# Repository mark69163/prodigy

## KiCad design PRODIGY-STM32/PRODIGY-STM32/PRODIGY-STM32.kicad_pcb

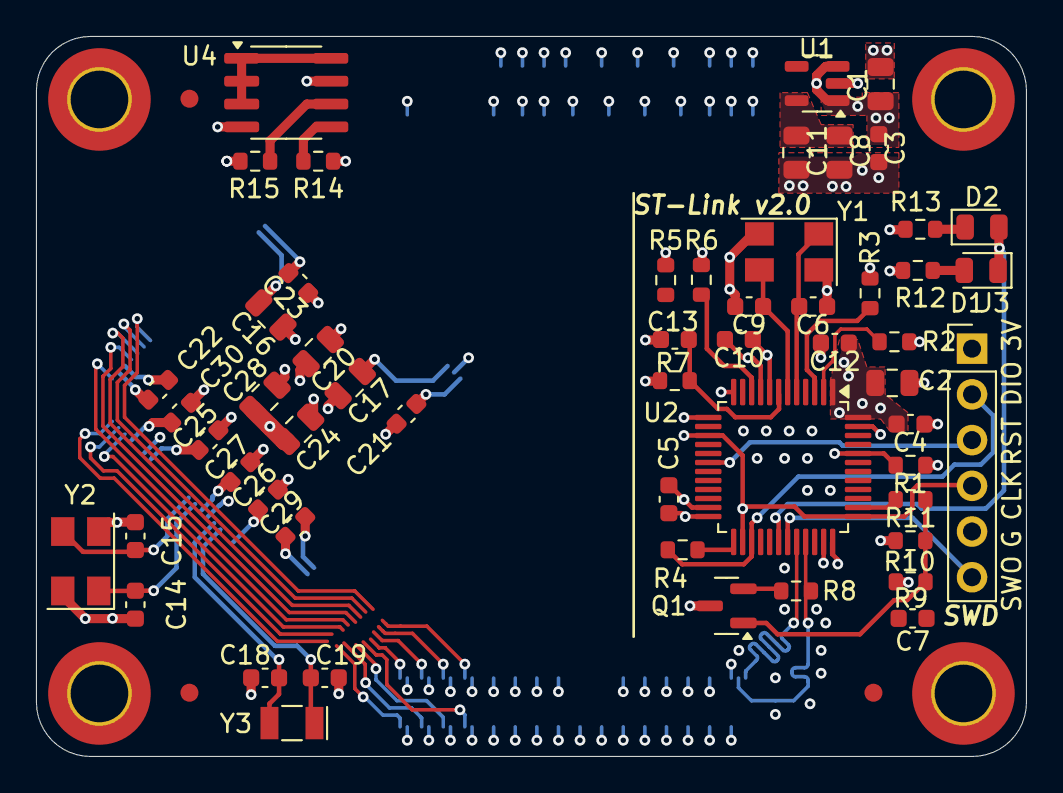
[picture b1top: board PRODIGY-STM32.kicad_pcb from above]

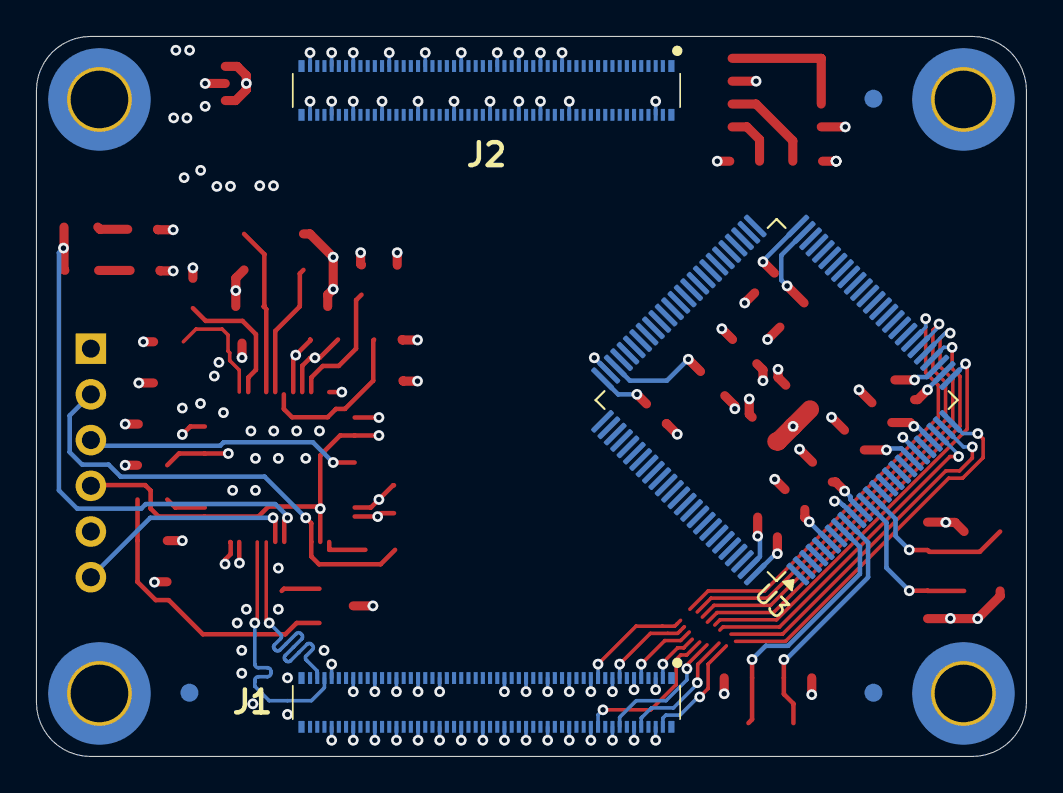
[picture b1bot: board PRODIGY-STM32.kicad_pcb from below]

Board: 4 copper layers, 55.0 x 40.0 mm, 68 parts (6 on the bottom side), 106 nets.

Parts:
C1, C2, C8, C11, C20, C24, C28: 10uF; C_0805_2012Metric
C3, C4, C5, C7, C10, C12, C13, C21, C22, C23, C25, C26, C27, C29, C30: 100nF; C_0603_1608Metric
C6, C9: 10pF; C_0603_1608Metric
C14, C15: 4.7pF; C_0603_1608Metric
C16, C17: 2.2uF; C_0805_2012Metric
C18, C19: 2.7pF; C_0603_1608Metric
D1, D2: LED; LED_0805_2012Metric
FID1, FID2, FID3, FID4, FID5, FID6: Fiducial; Fiducial_1mm_Mask3mm
H1, H2, H3, H4: MountingHole; MountingHole_3.2mm_M3_ISO7380_Pad_TopBottom
J1, J2: DF40C-100DP-04V-51; DF40C100DP04V51
J3: Conn_ARM_SWD_TagConnect_TC2030; PinHeader_1x06_P2.54mm_Vertical
Q1: BC850; SOT-23
R1, R7: 100k; R_0603_1608Metric
R2, R9, R10: 10k; R_0603_1608Metric
R3, R14, R15: DNP; R_0603_1608Metric
R4, R11: 100; R_0603_1608Metric
R5, R6: 4k7; R_0603_1608Metric
R8: 1k5; R_0603_1608Metric
R12, R13: 1k; R_0603_1608Metric
U1: AP2112K-3.3; SOT-23-5
U2: STM32F103C8Tx; LQFP-48_7x7mm_P0.5mm
U3: STM32F407VGTx; LQFP-100_14x14mm_P0.5mm
U4: M24C32-WMN6TP; SOIC-8_3.9x4.9mm_P1.27mm
Y1, Y2: 8MHz; Crystal_SMD_5032-4Pin_5.0x3.2mm
Y3: 32.768kHz; Crystal_SMD_MicroCrystal_CC7V-T1A-2Pin_3.2x1.5mm

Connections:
+3V3: C20.1, C21.1, C22.1, C23.1, C24.1, C25.1, C26.1, C27.1, C28.1, C29.1, C30.1, J2.12, J2.14, J2.16, J2.18, R14.1, R15.1, U3.6 (VBAT), U3.11 (VDD), U3.19 (VDD), U3.22 (VDDA), U3.28 (VDD), U3.50 (VDD), U3.75 (VDD), U3.100 (VDD), U4.1 (E0), U4.2 (E1), U4.3 (E2), U4.8 (VCC)
+5V: C1.1, C3.1, J2.13, J2.15, J2.17, J2.19, J2.21, J2.23, U1.1 (VIN), U1.3 (EN)
/Connector-1/ANALOG_BREAKOUT_PIEZO: J1.2, U3.31 (PA6)
/Connector-1/ANALOG_BREAKOUT_PT100: J1.8, U3.32 (PA7)
/Connector-1/ANALOG_HEATER_TEMPERATURE: J1.14, U3.30 (PA5)
/Connector-1/ANALOG_JOYSTICK_X: J1.13, U3.25 (PA2)
/Connector-1/ANALOG_JOYSTICK_Y: J1.7, U3.26 (PA3)
/Connector-1/ANALOG_MICROPHONE: J1.1, U3.29 (PA4)
/Connector-1/ANALOG_PHOTOTRANSISTOR: J1.19, U3.24 (PA1)
/Connector-1/ANALOG_POTENTIOMETER: J1.20, U3.23 (PA0)
/Connector-1/CAN_EN: J1.86, U3.84 (PD3)
/Connector-1/CAN_OUT_RX1: J1.83, U3.81 (PD0)
/Connector-1/CAN_OUT_TX1: J1.85, U3.82 (PD1)
/Connector-1/CAN_SILENT: J1.84, U3.85 (PD4)
/Connector-1/DIGITAL_BUTTON_IN_0: J1.53, U3.57 (PD10)
/Connector-1/DIGITAL_BUTTON_IN_1: J1.51, U3.58 (PD11)
/Connector-1/DIGITAL_BUTTON_IN_2: J1.49, U3.59 (PD12)
/Connector-1/DIGITAL_BUTTON_IN_3: J1.47, U3.60 (PD13)
/Connector-1/DIGITAL_BUZZER_OUT: J1.42, U3.36 (PB1)
/Connector-1/DIGITAL_HEATER_OUT: J1.48, U3.37 (PB2)
/Connector-1/DIGITAL_IR_EMITTER: J1.67, U3.33 (PC4)
/Connector-1/DIGITAL_IR_RECEIVER: J1.65, U3.34 (PC5)
/Connector-1/DIGITAL_LED_OUT_0: J1.43, U3.88 (PD7)
/Connector-1/DIGITAL_LED_OUT_1: J1.41, U3.61 (PD14)
/Connector-1/DIGITAL_LED_OUT_2: J1.44, U3.62 (PD15)
/Connector-1/DIGITAL_NEOPIXEL_OUT: J1.61, U3.35 (PB0)
/Connector-1/DIGITAL_RGB_B: J1.55, U3.4 (PE5)
/Connector-1/DIGITAL_RGB_G: J1.57, U3.3 (PE4)
/Connector-1/DIGITAL_RGB_R: J1.59, U3.5 (PE6)
/Connector-1/I2C_INTERRUPT_ACCEL: J1.73, U3.91 (PB5)
/Connector-1/I2C_INTERRUPT_KEYPAD: J1.71, U3.95 (PB8)
/Connector-1/MOTOR_CC_IN_1: J1.35, U3.97 (PE0)
/Connector-1/MOTOR_CC_IN_2: J1.36, U3.98 (PE1)
/Connector-1/MOTOR_PWM_OUT_1: J1.37, U3.1 (PE2)
/Connector-1/MOTOR_PWM_OUT_2: J1.38, U3.2 (PE3)
/Connector-1/SERIAL_OUT_RX1: J1.91, U3.68 (PA9)
/Connector-1/SERIAL_OUT_RX2: J1.90, U3.87 (PD6)
/Connector-1/SERIAL_OUT_TX1: J1.89, U3.69 (PA10)
/Connector-1/SERIAL_OUT_TX2: J1.92, U3.86 (PD5)
/Connector-1/SPI_CS_BREAKOUT: J1.72, U3.96 (PB9)
/Connector-1/SPI_CS_NFC: J1.56, U3.54 (PB15)
/Connector-1/SPI_CS_SEVENSEG: J1.68, U3.48 (PB11)
/Connector-1/SPI_CS_TFT: J1.66, U3.51 (PB12)
/Connector-1/SPI_IRQ_NFC: J1.54, U3.15 (PC0)
/Connector-1/SPI_MISO: J1.78, U3.17 (PC2)
/Connector-1/SPI_MOSI: J1.80, U3.18 (PC3)
/Connector-1/SPI_RST_NFC: J1.50, U3.16 (PC1)
/Connector-1/SPI_SCK: J1.74, U3.47 (PB10)
/Connector-1/SPI_TFT_DC: J1.62, U3.52 (PB13)
/Connector-1/SPI_TFT_RESET: J1.60, U3.53 (PB14)
/Connector-1/USB_DP-: J1.97, U2.32 (PA11)
/Connector-1/USB_HOST_ENABLE: J1.100, U3.77 (PA15)
/Connector-1/USB_HOST_FAULT: J1.99, U3.67 (PA8)
/Connector-1/USB_HOST_OUT_P+: J1.96, U3.71 (PA12)
/Connector-1/USB_HOST_OUT_P-: J1.98, U3.70 (PA11)
/Connector-2/MCU_GPIO_6: J2.72, U3.7 (PC13)
/Connector-2/MCU_GPIO_7: J2.63, U3.38 (PE7)
/Connector-2/MCU_GPIO_8: J2.61, U3.39 (PE8)
/Connector-2/MCU_GPIO_9: J2.62, U3.40 (PE9)
/Connector-2/MCU_GPIO_10: J2.58, U3.41 (PE10)
/Connector-2/MCU_GPIO_11: J2.64, U3.42 (PE11)
/Connector-2/MCU_GPIO_12: J2.69, U3.43 (PE12)
/Connector-2/MCU_GPIO_13: J2.74, U3.44 (PE13)
/Connector-2/MCU_GPIO_14: J2.45, U3.45 (PE14)
/Connector-2/MCU_GPIO_15: J2.49, U3.46 (PE15)
/Connector-2/MCU_RESET: J2.2, U3.14 (NRST)
/Connector-2/MCU_VREF: J2.24, U3.21 (VREF+)
/Connector-2/SD_CLK: J2.43, U3.80 (PC12)
/Connector-2/SD_CMD: J2.40, U3.83 (PD2)
/Connector-2/SD_DAT0: J2.37, U3.65 (PC8)
/Connector-2/SD_DAT1: J2.33, U3.66 (PC9)
/Connector-2/SD_DAT2: J2.31, U3.78 (PC10)
/Connector-2/SD_DAT3: J2.39, U3.79 (PC11)
/Connector-2/SD_DET: J2.26, U3.63 (PC6)
/Connector-2/SD_Enable: J2.25, U3.64 (PC7)
/mcu/BOOT: R1.1, U2.44 (BOOT0), U3.94 (BOOT0)
/mcu/SCL: J1.77, R15.2, U3.92 (PB6), U4.6 (SCL)
/mcu/SDA: J1.79, R14.2, U3.93 (PB7), U4.5 (SDA)
/mcu/T_RX: U2.13 (PA3), U3.56 (PD9)
/mcu/T_TX: U2.12 (PA2), U3.55 (PD8)
/st-link-v2/+3V3_STLINK: C2.1, C4.1, C5.1, C7.1, C8.1, C10.1, C11.1, C12.1, J3.1 (VCC), Q1.3 (C), R5.1, R7.1, R9.1, R12.1, U1.5 (VOUT), U2.1 (VBAT), U2.9 (VDDA), U2.24 (VDD), U2.36 (VDD), U2.48 (VDD)
/st-link-v2/CLK: J3.4 (SWCLK), U2.15 (PA5), U2.26 (PB13), U2.37 (PA14), U3.76 (PA14)
/st-link-v2/LED: D1.1 (K), D2.2 (A), U2.30 (PA9)
/st-link-v2/RENUM: R11.2, U2.38 (PA15)
/st-link-v2/RESET: C13.1, R7.2, U2.7 (NRST)
/st-link-v2/T_DIO: J3.2 (SWDIO), R4.1, U2.27 (PB14), U3.72 (PA13)
/st-link-v2/T_RST: J3.3 (~RESET), U2.18 (PB0), U3.90 (PB4)
/st-link-v2/T_SWO: J3.6 (SWO), U2.31 (PA10), U3.89 (PB3)
/st-link-v2/USB_D+: J1.95, R8.2, U2.33 (PA12)
GND: C1.2, C2.2, C3.2, C4.2, C5.2, C6.2, C7.2, C8.2, C9.2, C10.2, C11.2, C12.2, C13.2, C14.2, C15.2, C16.2, C17.2, C18.2, C19.2, C20.2, C21.2, C22.2, C23.2, C24.2, C25.2, C26.2, C27.2, C28.2, C29.2, C30.2, J1.3, J1.4, J1.9, J1.10, J1.15, J1.16, J1.21, J1.22, J1.27, J1.28, J1.33, J1.34, J1.39, J1.40, J1.45, J1.46, J1.52, J1.58, J1.63, J1.64, J1.69, J1.70, J1.75, J1.76, J1.81, J1.82, J1.87, J1.88, J1.93, J1.94, J2.4, J2.28, J2.29, J2.35, J2.36, J2.41, J2.42, J2.47, J2.50, J2.57, J2.60, J2.67, J2.70, J2.77, J2.80, J2.87, J2.88, J2.93, J2.94, J2.99, J2.100, J3.5 (GND), R1.2, R2.2, R3.2, R6.2, R10.2, R13.2, U1.2 (GND), U2.8 (VSSA), U2.23 (VSS), U2.35 (VSS), U2.47 (VSS), U3.10 (VSS), U3.20 (VSSA), U3.27 (VSS), U3.74 (VSS), U3.99 (VSS), U4.4 (VSS), U4.7 (~WC), Y1.2, Y1.4, Y2.2, Y2.4
unnamed: D1.2 (A), R12.2
unnamed: D2.1 (K), R13.1
unnamed: Q1.1 (B), R9.2, R10.1, R11.1
unnamed: Q1.2 (E), R8.1
unnamed: R5.2, R6.1, U2.10 (PA0)
unnamed: R4.2, U2.25 (PB12)
unnamed: R2.1, U2.2 (PC13)
unnamed: R3.1, U2.3 (PC14)
unnamed: C6.1, U2.5 (PD0), Y1.1
unnamed: C9.1, U2.6 (PD1), Y1.3
unnamed: C19.1, U3.8 (PC14), Y3.1
unnamed: C18.1, U3.9 (PC15), Y3.2
unnamed: C14.1, U3.12 (PH0), Y2.1
unnamed: C15.1, U3.13 (PH1), Y2.3
unnamed: C16.1, U3.49 (VCAP_1)
unnamed: C17.1, U3.73 (VCAP_2)

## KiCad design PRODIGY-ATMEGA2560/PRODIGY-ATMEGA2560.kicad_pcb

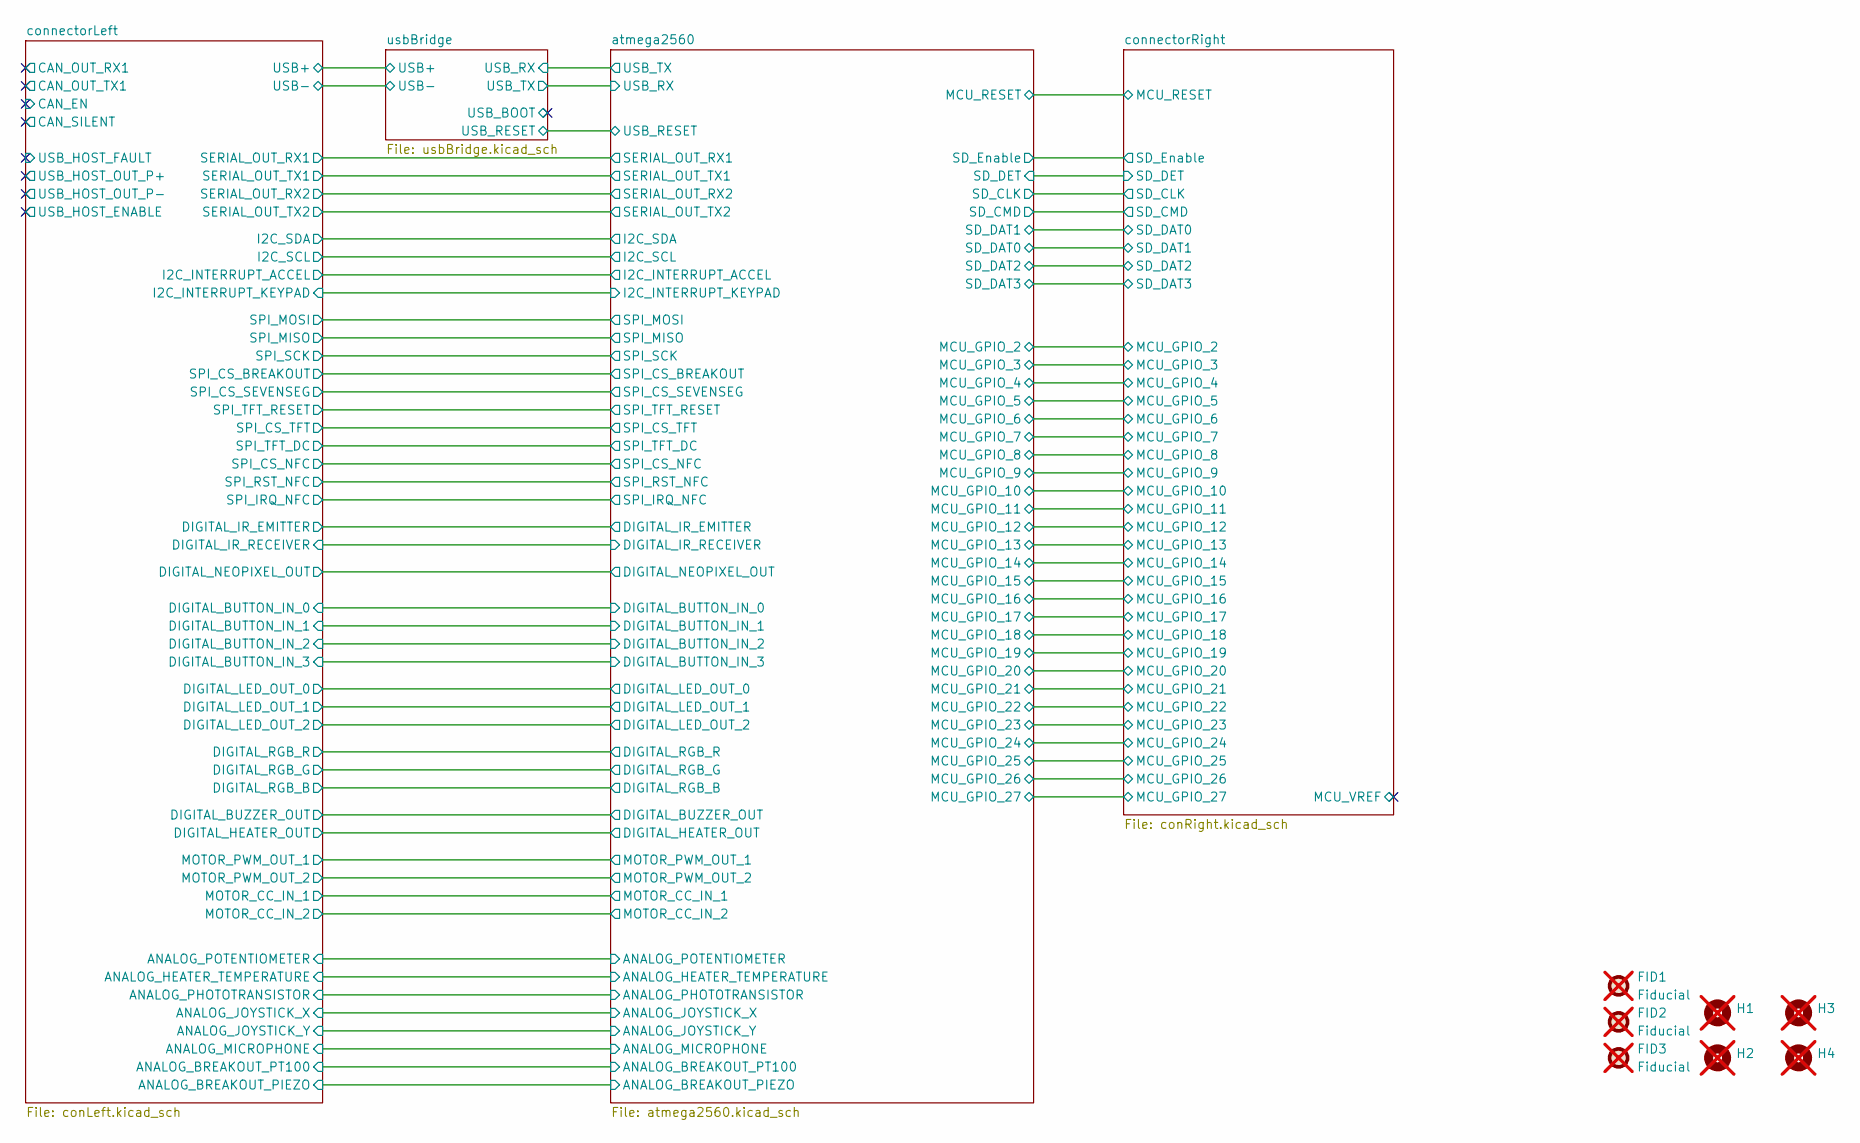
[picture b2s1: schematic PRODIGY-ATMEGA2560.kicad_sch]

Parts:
FID1, FID2, FID3: Fiducial; Fiducial_1mm_Mask3mm; not fitted
H1, H2, H3, H4: MountingHole; MountingHole_3.2mm_M3_ISO7380_Pad_TopBottom; not fitted

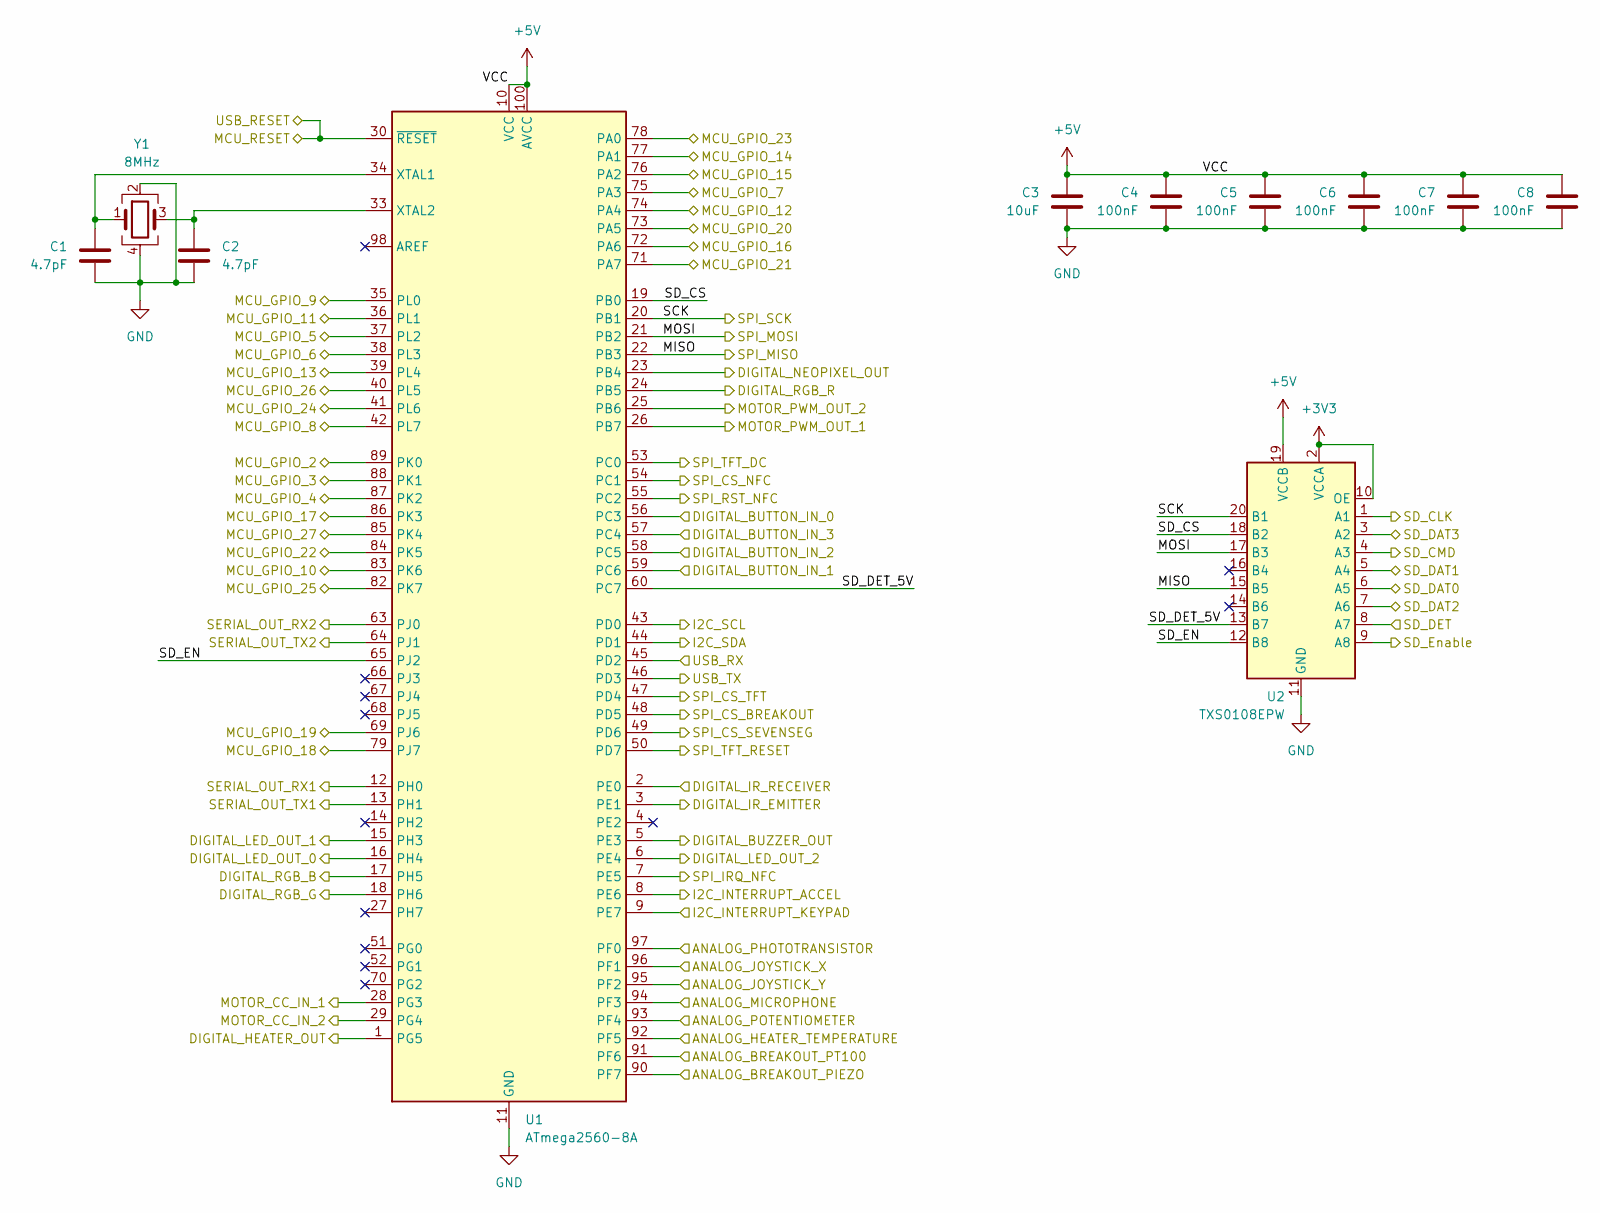
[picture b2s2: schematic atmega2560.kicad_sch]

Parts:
C1, C2: 4.7pF; C_0603_1608Metric
C3: 10uF; C_0805_2012Metric
C4, C5, C6, C7, C8: 100nF; C_0603_1608Metric
U1: ATmega2560-8A; TQFP-100_14x14mm_P0.5mm
U2: TXS0108EPW; TSSOP-20_4.4x6.5mm_P0.65mm
Y1: 8MHz; Crystal_SMD_5032-4Pin_5.0x3.2mm

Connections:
+3V3: U2.2 (VCCA), U2.10 (OE); also elsewhere on the board
+5V: C3.1, C4.1, C5.1, C6.1, C7.1, C8.1, U1.10 (VCC), U1.31 (VCC), U1.61 (VCC), U1.80 (VCC), U1.100 (AVCC), U2.19 (VCCB); also elsewhere on the board
/atmega2560/ANALOG_BREAKOUT_PIEZO: U1.90 (PF7); also elsewhere on the board
/atmega2560/ANALOG_BREAKOUT_PT100: U1.91 (PF6); also elsewhere on the board
/atmega2560/ANALOG_HEATER_TEMPERATURE: U1.92 (PF5); also elsewhere on the board
/atmega2560/ANALOG_JOYSTICK_X: U1.96 (PF1); also elsewhere on the board
/atmega2560/ANALOG_JOYSTICK_Y: U1.95 (PF2); also elsewhere on the board
/atmega2560/ANALOG_MICROPHONE: U1.94 (PF3); also elsewhere on the board
/atmega2560/ANALOG_PHOTOTRANSISTOR: U1.97 (PF0); also elsewhere on the board
/atmega2560/ANALOG_POTENTIOMETER: U1.93 (PF4); also elsewhere on the board
/atmega2560/DIGITAL_BUTTON_IN_0: U1.56 (PC3); also elsewhere on the board
/atmega2560/DIGITAL_BUTTON_IN_1: U1.59 (PC6); also elsewhere on the board
/atmega2560/DIGITAL_BUTTON_IN_2: U1.58 (PC5); also elsewhere on the board
/atmega2560/DIGITAL_BUTTON_IN_3: U1.57 (PC4); also elsewhere on the board
/atmega2560/DIGITAL_BUZZER_OUT: U1.5 (PE3); also elsewhere on the board
/atmega2560/DIGITAL_HEATER_OUT: U1.1 (PG5); also elsewhere on the board
/atmega2560/DIGITAL_IR_EMITTER: U1.3 (PE1); also elsewhere on the board
/atmega2560/DIGITAL_IR_RECEIVER: U1.2 (PE0); also elsewhere on the board
/atmega2560/DIGITAL_LED_OUT_0: U1.16 (PH4); also elsewhere on the board
/atmega2560/DIGITAL_LED_OUT_1: U1.15 (PH3); also elsewhere on the board
/atmega2560/DIGITAL_LED_OUT_2: U1.6 (PE4); also elsewhere on the board
/atmega2560/DIGITAL_NEOPIXEL_OUT: U1.23 (PB4); also elsewhere on the board
/atmega2560/DIGITAL_RGB_B: U1.17 (PH5); also elsewhere on the board
/atmega2560/DIGITAL_RGB_G: U1.18 (PH6); also elsewhere on the board
/atmega2560/DIGITAL_RGB_R: U1.24 (PB5); also elsewhere on the board
/atmega2560/I2C_INTERRUPT_ACCEL: U1.8 (PE6); also elsewhere on the board
/atmega2560/I2C_INTERRUPT_KEYPAD: U1.9 (PE7); also elsewhere on the board
/atmega2560/I2C_SCL: U1.43 (PD0); also elsewhere on the board
/atmega2560/I2C_SDA: U1.44 (PD1); also elsewhere on the board
/atmega2560/MCU_GPIO_2: U1.89 (PK0); also elsewhere on the board
/atmega2560/MCU_GPIO_3: U1.88 (PK1); also elsewhere on the board
/atmega2560/MCU_GPIO_4: U1.87 (PK2); also elsewhere on the board
/atmega2560/MCU_GPIO_5: U1.37 (PL2); also elsewhere on the board
/atmega2560/MCU_GPIO_6: U1.38 (PL3); also elsewhere on the board
/atmega2560/MCU_GPIO_7: U1.75 (PA3); also elsewhere on the board
/atmega2560/MCU_GPIO_8: U1.42 (PL7); also elsewhere on the board
/atmega2560/MCU_GPIO_9: U1.35 (PL0); also elsewhere on the board
/atmega2560/MCU_GPIO_10: U1.83 (PK6); also elsewhere on the board
/atmega2560/MCU_GPIO_11: U1.36 (PL1); also elsewhere on the board
/atmega2560/MCU_GPIO_12: U1.74 (PA4); also elsewhere on the board
/atmega2560/MCU_GPIO_13: U1.39 (PL4); also elsewhere on the board
/atmega2560/MCU_GPIO_14: U1.77 (PA1); also elsewhere on the board
/atmega2560/MCU_GPIO_15: U1.76 (PA2); also elsewhere on the board
/atmega2560/MCU_GPIO_16: U1.72 (PA6); also elsewhere on the board
/atmega2560/MCU_GPIO_17: U1.86 (PK3); also elsewhere on the board
/atmega2560/MCU_GPIO_18: U1.79 (PJ7); also elsewhere on the board
/atmega2560/MCU_GPIO_19: U1.69 (PJ6); also elsewhere on the board
/atmega2560/MCU_GPIO_20: U1.73 (PA5); also elsewhere on the board
/atmega2560/MCU_GPIO_21: U1.71 (PA7); also elsewhere on the board
/atmega2560/MCU_GPIO_22: U1.84 (PK5); also elsewhere on the board
/atmega2560/MCU_GPIO_23: U1.78 (PA0); also elsewhere on the board
/atmega2560/MCU_GPIO_24: U1.41 (PL6); also elsewhere on the board
/atmega2560/MCU_GPIO_25: U1.82 (PK7); also elsewhere on the board
/atmega2560/MCU_GPIO_26: U1.40 (PL5); also elsewhere on the board
/atmega2560/MCU_GPIO_27: U1.85 (PK4); also elsewhere on the board
/atmega2560/MCU_RESET: U1.30 (~RESET); also elsewhere on the board
/atmega2560/MISO: U1.22 (PB3), U2.15 (B5); also elsewhere on the board
/atmega2560/MOSI: U1.21 (PB2), U2.17 (B3); also elsewhere on the board
/atmega2560/MOTOR_CC_IN_1: U1.28 (PG3); also elsewhere on the board
/atmega2560/MOTOR_CC_IN_2: U1.29 (PG4); also elsewhere on the board
/atmega2560/MOTOR_PWM_OUT_1: U1.26 (PB7); also elsewhere on the board
/atmega2560/MOTOR_PWM_OUT_2: U1.25 (PB6); also elsewhere on the board
/atmega2560/SCK: U1.20 (PB1), U2.20 (B1); also elsewhere on the board
/atmega2560/SD_CLK: U2.1 (A1); also elsewhere on the board
/atmega2560/SD_CMD: U2.4 (A3); also elsewhere on the board
/atmega2560/SD_CS: U1.19 (PB0), U2.18 (B2)
/atmega2560/SD_DAT0: U2.6 (A5); also elsewhere on the board
/atmega2560/SD_DAT1: U2.5 (A4); also elsewhere on the board
/atmega2560/SD_DAT2: U2.7 (A6); also elsewhere on the board
/atmega2560/SD_DAT3: U2.3 (A2); also elsewhere on the board
/atmega2560/SD_DET: U2.8 (A7); also elsewhere on the board
/atmega2560/SD_DET_5V: U1.60 (PC7), U2.13 (B7)
/atmega2560/SD_EN: U1.65 (PJ2), U2.12 (B8)
/atmega2560/SD_Enable: U2.9 (A8); also elsewhere on the board
/atmega2560/SERIAL_OUT_RX1: U1.12 (PH0); also elsewhere on the board
/atmega2560/SERIAL_OUT_RX2: U1.63 (PJ0); also elsewhere on the board
/atmega2560/SERIAL_OUT_TX1: U1.13 (PH1); also elsewhere on the board
/atmega2560/SERIAL_OUT_TX2: U1.64 (PJ1); also elsewhere on the board
/atmega2560/SPI_CS_BREAKOUT: U1.48 (PD5); also elsewhere on the board
/atmega2560/SPI_CS_NFC: U1.54 (PC1); also elsewhere on the board
/atmega2560/SPI_CS_SEVENSEG: U1.49 (PD6); also elsewhere on the board
/atmega2560/SPI_CS_TFT: U1.47 (PD4); also elsewhere on the board
/atmega2560/SPI_IRQ_NFC: U1.7 (PE5); also elsewhere on the board
/atmega2560/SPI_RST_NFC: U1.55 (PC2); also elsewhere on the board
/atmega2560/SPI_TFT_DC: U1.53 (PC0); also elsewhere on the board
/atmega2560/SPI_TFT_RESET: U1.50 (PD7); also elsewhere on the board
/atmega2560/USB_RX: U1.45 (PD2); also elsewhere on the board
/atmega2560/USB_TX: U1.46 (PD3); also elsewhere on the board
GND: C1.2, C2.2, C3.2, C4.2, C5.2, C6.2, C7.2, C8.2, U1.11 (GND), U1.32 (GND), U1.62 (GND), U1.81 (GND), U1.99 (GND), U2.11 (GND), Y1.2, Y1.4; also elsewhere on the board
unnamed: C1.1, U1.34 (XTAL1), Y1.1
unnamed: C2.1, U1.33 (XTAL2), Y1.3

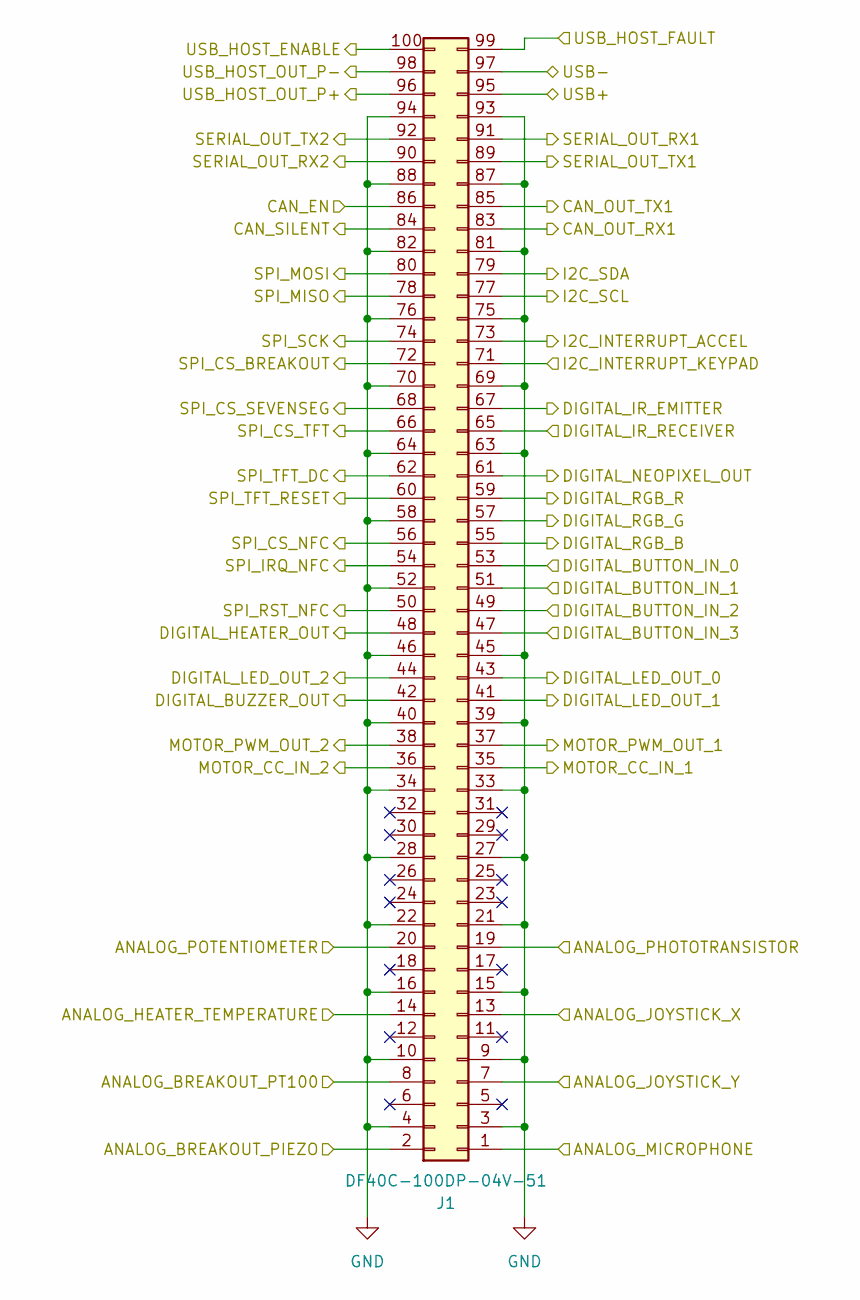
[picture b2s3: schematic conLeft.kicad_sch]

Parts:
J1: DF40C-100DP-04V-51; DF40C100DP04V51

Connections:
/atmega2560/ANALOG_BREAKOUT_PIEZO: J1.2; also elsewhere on the board
/atmega2560/ANALOG_BREAKOUT_PT100: J1.8; also elsewhere on the board
/atmega2560/ANALOG_HEATER_TEMPERATURE: J1.14; also elsewhere on the board
/atmega2560/ANALOG_JOYSTICK_X: J1.13; also elsewhere on the board
/atmega2560/ANALOG_JOYSTICK_Y: J1.7; also elsewhere on the board
/atmega2560/ANALOG_MICROPHONE: J1.1; also elsewhere on the board
/atmega2560/ANALOG_PHOTOTRANSISTOR: J1.19; also elsewhere on the board
/atmega2560/ANALOG_POTENTIOMETER: J1.20; also elsewhere on the board
/atmega2560/DIGITAL_BUTTON_IN_0: J1.53; also elsewhere on the board
/atmega2560/DIGITAL_BUTTON_IN_1: J1.51; also elsewhere on the board
/atmega2560/DIGITAL_BUTTON_IN_2: J1.49; also elsewhere on the board
/atmega2560/DIGITAL_BUTTON_IN_3: J1.47; also elsewhere on the board
/atmega2560/DIGITAL_BUZZER_OUT: J1.42; also elsewhere on the board
/atmega2560/DIGITAL_HEATER_OUT: J1.48; also elsewhere on the board
/atmega2560/DIGITAL_IR_EMITTER: J1.67; also elsewhere on the board
/atmega2560/DIGITAL_IR_RECEIVER: J1.65; also elsewhere on the board
/atmega2560/DIGITAL_LED_OUT_0: J1.43; also elsewhere on the board
/atmega2560/DIGITAL_LED_OUT_1: J1.41; also elsewhere on the board
/atmega2560/DIGITAL_LED_OUT_2: J1.44; also elsewhere on the board
/atmega2560/DIGITAL_NEOPIXEL_OUT: J1.61; also elsewhere on the board
/atmega2560/DIGITAL_RGB_B: J1.55; also elsewhere on the board
/atmega2560/DIGITAL_RGB_G: J1.57; also elsewhere on the board
/atmega2560/DIGITAL_RGB_R: J1.59; also elsewhere on the board
/atmega2560/I2C_INTERRUPT_ACCEL: J1.73; also elsewhere on the board
/atmega2560/I2C_INTERRUPT_KEYPAD: J1.71; also elsewhere on the board
/atmega2560/I2C_SCL: J1.77; also elsewhere on the board
/atmega2560/I2C_SDA: J1.79; also elsewhere on the board
/atmega2560/MISO: J1.78; also elsewhere on the board
/atmega2560/MOSI: J1.80; also elsewhere on the board
/atmega2560/MOTOR_CC_IN_1: J1.35; also elsewhere on the board
/atmega2560/MOTOR_CC_IN_2: J1.36; also elsewhere on the board
/atmega2560/MOTOR_PWM_OUT_1: J1.37; also elsewhere on the board
/atmega2560/MOTOR_PWM_OUT_2: J1.38; also elsewhere on the board
/atmega2560/SCK: J1.74; also elsewhere on the board
/atmega2560/SERIAL_OUT_RX1: J1.91; also elsewhere on the board
/atmega2560/SERIAL_OUT_RX2: J1.90; also elsewhere on the board
/atmega2560/SERIAL_OUT_TX1: J1.89; also elsewhere on the board
/atmega2560/SERIAL_OUT_TX2: J1.92; also elsewhere on the board
/atmega2560/SPI_CS_BREAKOUT: J1.72; also elsewhere on the board
/atmega2560/SPI_CS_NFC: J1.56; also elsewhere on the board
/atmega2560/SPI_CS_SEVENSEG: J1.68; also elsewhere on the board
/atmega2560/SPI_CS_TFT: J1.66; also elsewhere on the board
/atmega2560/SPI_IRQ_NFC: J1.54; also elsewhere on the board
/atmega2560/SPI_RST_NFC: J1.50; also elsewhere on the board
/atmega2560/SPI_TFT_DC: J1.62; also elsewhere on the board
/atmega2560/SPI_TFT_RESET: J1.60; also elsewhere on the board
/connectorLeft/CAN_EN: J1.86
/connectorLeft/CAN_OUT_RX1: J1.83
/connectorLeft/CAN_OUT_TX1: J1.85
/connectorLeft/CAN_SILENT: J1.84
/connectorLeft/USB+: J1.95; also elsewhere on the board
/connectorLeft/USB-: J1.97; also elsewhere on the board
/connectorLeft/USB_HOST_ENABLE: J1.100
/connectorLeft/USB_HOST_FAULT: J1.99
/connectorLeft/USB_HOST_OUT_P+: J1.96
/connectorLeft/USB_HOST_OUT_P-: J1.98
GND: J1.3, J1.4, J1.9, J1.10, J1.15, J1.16, J1.21, J1.22, J1.27, J1.28, J1.33, J1.34, J1.39, J1.40, J1.45, J1.46, J1.52, J1.58, J1.63, J1.64, J1.69, J1.70, J1.75, J1.76, J1.81, J1.82, J1.87, J1.88, J1.93, J1.94; also elsewhere on the board

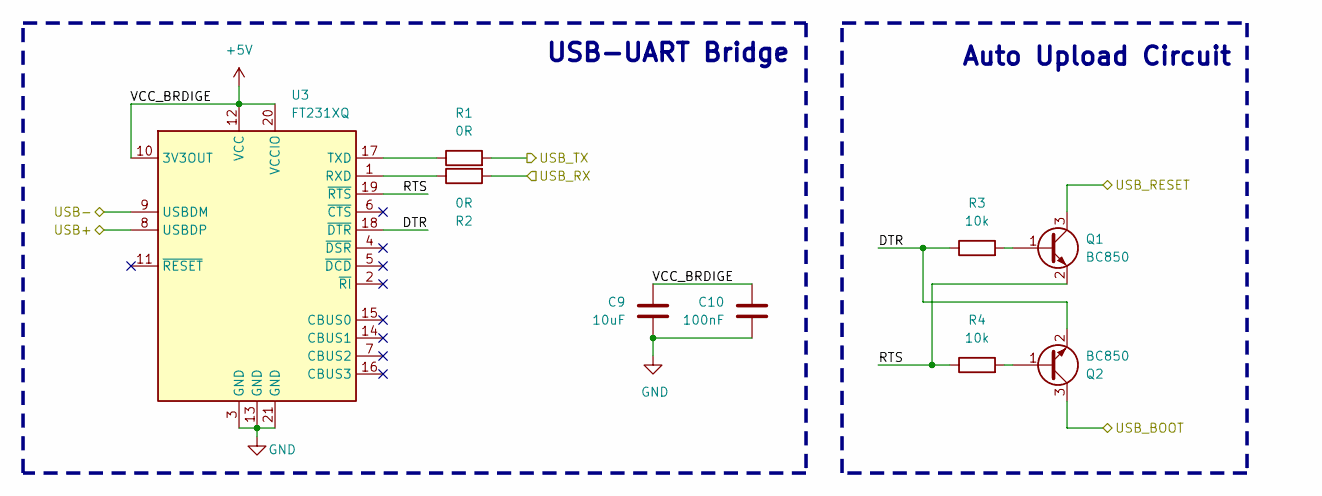
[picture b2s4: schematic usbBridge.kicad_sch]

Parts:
C9: 10uF; C_0805_2012Metric
C10: 100nF; C_0603_1608Metric
Q1, Q2: BC850; SOT-23
R1, R2: 0R; R_0603_1608Metric
R3, R4: 10k; R_0603_1608Metric
U3: FT231XQ; QFN-20-1EP_4x4mm_P0.5mm_EP2.5x2.5mm

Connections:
+5V: C9.1, C10.1, U3.10 (3V3OUT), U3.12 (VCC), U3.20 (VCCIO); also elsewhere on the board
/atmega2560/MCU_RESET: Q1.3 (C); also elsewhere on the board
/atmega2560/USB_RX: R1.2; also elsewhere on the board
/atmega2560/USB_TX: R2.2; also elsewhere on the board
/connectorLeft/USB+: U3.8 (USBDP); also elsewhere on the board
/connectorLeft/USB-: U3.9 (USBDM); also elsewhere on the board
/usbBridge/DTR: Q2.2 (E), R3.1, U3.18 (~DTR)
/usbBridge/RTS: Q1.2 (E), R4.1, U3.19 (~RTS)
/usbBridge/USB_BOOT: Q2.3 (C)
GND: C9.2, C10.2, U3.3 (GND), U3.13 (GND), U3.21 (GND); also elsewhere on the board
unnamed: Q1.1 (B), R3.2
unnamed: Q2.1 (B), R4.2
unnamed: R2.1, U3.1 (RXD)
unnamed: R1.1, U3.17 (TXD)

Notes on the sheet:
USB-UART Bridge
Auto Upload Circuit

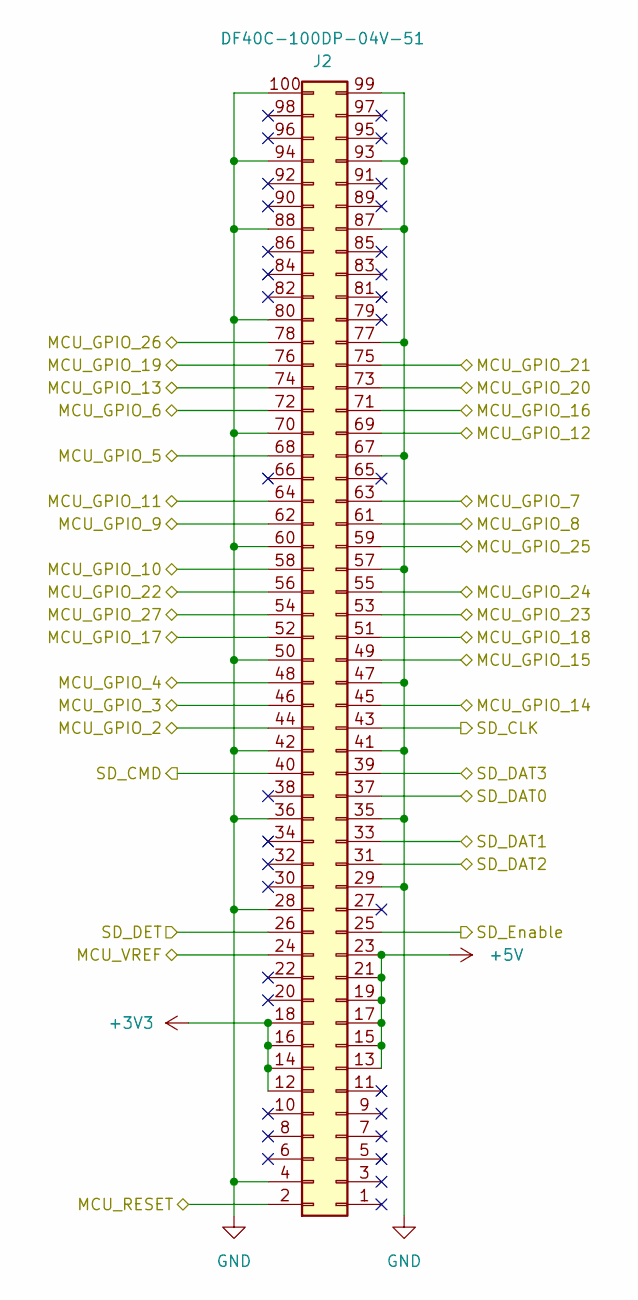
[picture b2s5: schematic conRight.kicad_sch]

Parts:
J2: DF40C-100DP-04V-51; DF40C100DP04V51

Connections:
+3V3: J2.12, J2.14, J2.16, J2.18; also elsewhere on the board
+5V: J2.13, J2.15, J2.17, J2.19, J2.21, J2.23; also elsewhere on the board
/atmega2560/MCU_GPIO_2: J2.44; also elsewhere on the board
/atmega2560/MCU_GPIO_3: J2.46; also elsewhere on the board
/atmega2560/MCU_GPIO_4: J2.48; also elsewhere on the board
/atmega2560/MCU_GPIO_5: J2.68; also elsewhere on the board
/atmega2560/MCU_GPIO_6: J2.72; also elsewhere on the board
/atmega2560/MCU_GPIO_7: J2.63; also elsewhere on the board
/atmega2560/MCU_GPIO_8: J2.61; also elsewhere on the board
/atmega2560/MCU_GPIO_9: J2.62; also elsewhere on the board
/atmega2560/MCU_GPIO_10: J2.58; also elsewhere on the board
/atmega2560/MCU_GPIO_11: J2.64; also elsewhere on the board
/atmega2560/MCU_GPIO_12: J2.69; also elsewhere on the board
/atmega2560/MCU_GPIO_13: J2.74; also elsewhere on the board
/atmega2560/MCU_GPIO_14: J2.45; also elsewhere on the board
/atmega2560/MCU_GPIO_15: J2.49; also elsewhere on the board
/atmega2560/MCU_GPIO_16: J2.71; also elsewhere on the board
/atmega2560/MCU_GPIO_17: J2.52; also elsewhere on the board
/atmega2560/MCU_GPIO_18: J2.51; also elsewhere on the board
/atmega2560/MCU_GPIO_19: J2.76; also elsewhere on the board
/atmega2560/MCU_GPIO_20: J2.73; also elsewhere on the board
/atmega2560/MCU_GPIO_21: J2.75; also elsewhere on the board
/atmega2560/MCU_GPIO_22: J2.56; also elsewhere on the board
/atmega2560/MCU_GPIO_23: J2.53; also elsewhere on the board
/atmega2560/MCU_GPIO_24: J2.55; also elsewhere on the board
/atmega2560/MCU_GPIO_25: J2.59; also elsewhere on the board
/atmega2560/MCU_GPIO_26: J2.78; also elsewhere on the board
/atmega2560/MCU_GPIO_27: J2.54; also elsewhere on the board
/atmega2560/MCU_RESET: J2.2; also elsewhere on the board
/atmega2560/SD_CLK: J2.43; also elsewhere on the board
/atmega2560/SD_CMD: J2.40; also elsewhere on the board
/atmega2560/SD_DAT0: J2.33; also elsewhere on the board
/atmega2560/SD_DAT1: J2.37; also elsewhere on the board
/atmega2560/SD_DAT2: J2.31; also elsewhere on the board
/atmega2560/SD_DAT3: J2.39; also elsewhere on the board
/atmega2560/SD_DET: J2.26; also elsewhere on the board
/atmega2560/SD_Enable: J2.25; also elsewhere on the board
/connectorRight/MCU_VREF: J2.24
GND: J2.4, J2.28, J2.29, J2.35, J2.36, J2.41, J2.42, J2.47, J2.50, J2.57, J2.60, J2.67, J2.70, J2.77, J2.80, J2.87, J2.88, J2.93, J2.94, J2.99, J2.100; also elsewhere on the board

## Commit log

2024-05-21 project restructure done. Hierarchical sheet done. Outputs/breakouts sheet done
2024-05-22 Finished I2C device and bus schematics. Added logic level translation.
2024-05-23 SPI SD CARD circuit added.
2024-05-23 Finished neopixel and button's schematic.
2024-05-23 LEDs schematic done.
2024-05-25 Digital section done.
2024-05-25 CAN schematic done
2024-05-26 SPI NFC schematic done.
2024-05-26 Analog schematic finished, except the joystick part.
2024-05-28 2-axis joystick footprint and sybmbol created. Analog-side done.
2024-05-29 Added pins to MCU. Added Decoder for SPI SS-Multiplexing.
2024-06-03 Added proper debounce filter elements to buttons.
2024-06-04 Esp32 motherboard schematic done.
2024-06-04 Submitted V0 for evaluation. Avaiting feedback.
2024-06-19 MCU schematic done. Started Analog design.
2024-06-20 Finished v0.1 schematic.
2024-06-22 MBT Schematic improved
2024-06-23 schematic v0.2 finalized
2024-06-24 changed breakout connectors and bpc size
2024-06-25 ESP32 schematic complete.
2024-06-26 Started STM32. Finished connectors and ST-LINK V2 schematic.
2024-06-29 stm32 schematic finished
2024-07-02 ATMEGA2560 schematic finished
2024-07-03 Motherboard footprints assigned.
2024-07-04 All footprint assosiations have been made across all schematics.
2024-07-06 STM32 bom done.
2024-07-06 ESP32 and ATMEGA bom done.
2024-07-06 Shcematic fixes to ESP32
2024-07-10 finished motherboard bom and updated footprints
2024-07-11 TOTAL BOM finalized.
2024-08-01 Motherboard PCB layout started.
2024-08-07 Motherboard PCB layout started
2024-08-09 Analog lazout done
2024-08-14 Motherboard layout done, testpoints still remain
2024-08-21 motherboard layout and labeling done
2024-08-23 Resistor array fixed, layout main components locked, high speed routing done
2024-08-26 did some routing
2024-08-29 lot more routing on the motherboard
2024-09-06 motherboard bulk routing mostly done, loads of vias placed, should be done with one days work
2024-09-10 Main routing on motherboard is done.
2024-09-12 nice routing done. nfc antenna close to done
2024-09-15 Fixed postion error on carrier, created nfc antenna
2024-09-15 Laberls fixed
2024-09-15 Power routing done...not nicely tho
2024-09-15 via stitching done
2024-09-17 testpoint labeling done.
2024-09-17 DRC done. motherboard done.
2024-09-17 revision control labeled
2024-09-17 motherboard production file done
2024-09-19 Atmega layout done. orientation and alignment testing done. routing started.
2024-09-22 vias done, some routing done. analog routing done
2024-09-27 major routing done on atmega board.
2024-09-29 Atmega board routing and power planes done. via stitching and labeling is needed
2024-09-30 DRC ran with 0 errors
2024-09-30 atmega board done, labeling done, gerber export done,
2024-10-01 stm32 started, footprints updated, lazout started
2024-10-09 stm32 layout done, schematic swd coinnector updated
2024-10-14 stlink wiring done, power vias placed, anlog routing almost done
2025-03-09 v0.1.1 schematic and pcb updated. gerbers exported, ready for production
